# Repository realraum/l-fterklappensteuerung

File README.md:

# r3 Lüfterklappensteuerung

Damper-Control for ventilation exhaust system in realraum.

## Overview

The state of three dampers (open / closed) and one fan (running / not running)need to be controlled electronically.
Additionally two touchscreen interfaces shall be created to controll the damper states.

The three dampers control exhaust of :
- Lasercutter
- Atomic absorption spectrometer
- Laminaflow

The lasercutter is in a separate room with a separate touchscreen interface.

##### Constraints:

If a damper has been opened in one room, it can only be closed via the interface in that room. This is a safty measure so that dampers 
are not closed from a separate room by people unaware that the exhaust is still in use.

## Contents

### elektronik

see this folder on how to connect stuff.

### firmware

this folder contains the firmware for the uc

The µCs communicate via PJON protocol. At least one raspberry will communicate via usb-serial with one of the µC. Each µC can be a bridge between usb-serial and PJON-bus.

### mechanik

The dampers are controlled by cheap motors from neuhold.
Their position is known via a photoelectric fork and a lasercut disk with slots.

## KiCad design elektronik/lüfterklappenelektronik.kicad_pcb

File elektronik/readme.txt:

===== µC =====

ATMega32U4
5V
16MHz

===== 230VAC Lüfter =====

wird geschalten mit: Neuhold SSR Typ ZG3NC-240B
hängt im Phasenleiter.
Datasheet: http://www.ndu.cl/pdf/0509040FT.pdf
Schaltleistung: 40A mit eingebautem Snubber. bei induktiven Lasten: 40% Strom der 40A sind ok --> passt für unseren Motor uns seiner Startlastspitzen.

SSR zieht laut Datenblatt maximal 40mA
laut Tests: <13mA bei 5V und <6mA bei 3V (und <11mA bei 5V mit 100 Ohm Widerstand in Serie weil weniger Spannung am SSR anliegt was auf den Stromverbrauch rückwirkt)
-> müsste mit teensy2 pin als Senke fast ohne Transistorschalter direkt zu schalten möglich sein.
  da atmega32u4 laut datenblatt 20mA permanent per IO senken kann solange die Summe einer im Datenblatt definierten Gruppe von Ports nicht 100mA überschreitet.

Zusätzlich: Varistor für 230V parallel zum SSR:
--> S7K275 welche im r3 sind
oder alternativ S14K680 von Neuhold
oder notfalls: 2x S10K150 in Serie

generelle Infos:
http://www.crydom.com/en/tech/whitepapers/ac_mc_whitepaper.pdf
http://forum.arduino.cc/index.php?topic=114209.0

off leakage: 10mA = 10mA (SSR) + 0mA (Varistor)

===== 12V Getriebemotoren für Lüfterklappen =====

Wird geschalten mit PowerMosFET und Freilaufdiode.

MosFET: IPP029N06N, reicht für 5V
     (alternativ: IRLR8743pbf)

Freilaufdiode parallel zum Motor, gegen Stromrichtung, sollte für >8A dimensioniert sein
SBL10L25 od. Ähnliches

===== Gabellichtschranken =====

2k2 Ohm(?) an K Ausgang um Widerstand der Photodiode zu balancieren.

120 Ohm Vorwiderstand für die LED

===== Drucksensor =====
BMP280

==== TODO ====

test SSR directly am Teensy:

SSR LED pulls <=19mA per test and 40mA per datasheet
We _could_probably connect it directly to the Teensy via 12 Ohm R
or maybe 47Ohm R which means 2V drop on 40mA and 0.5V drop on 10mA so we may naturally limit the current.
Relay LED minimum Voltage is 3V

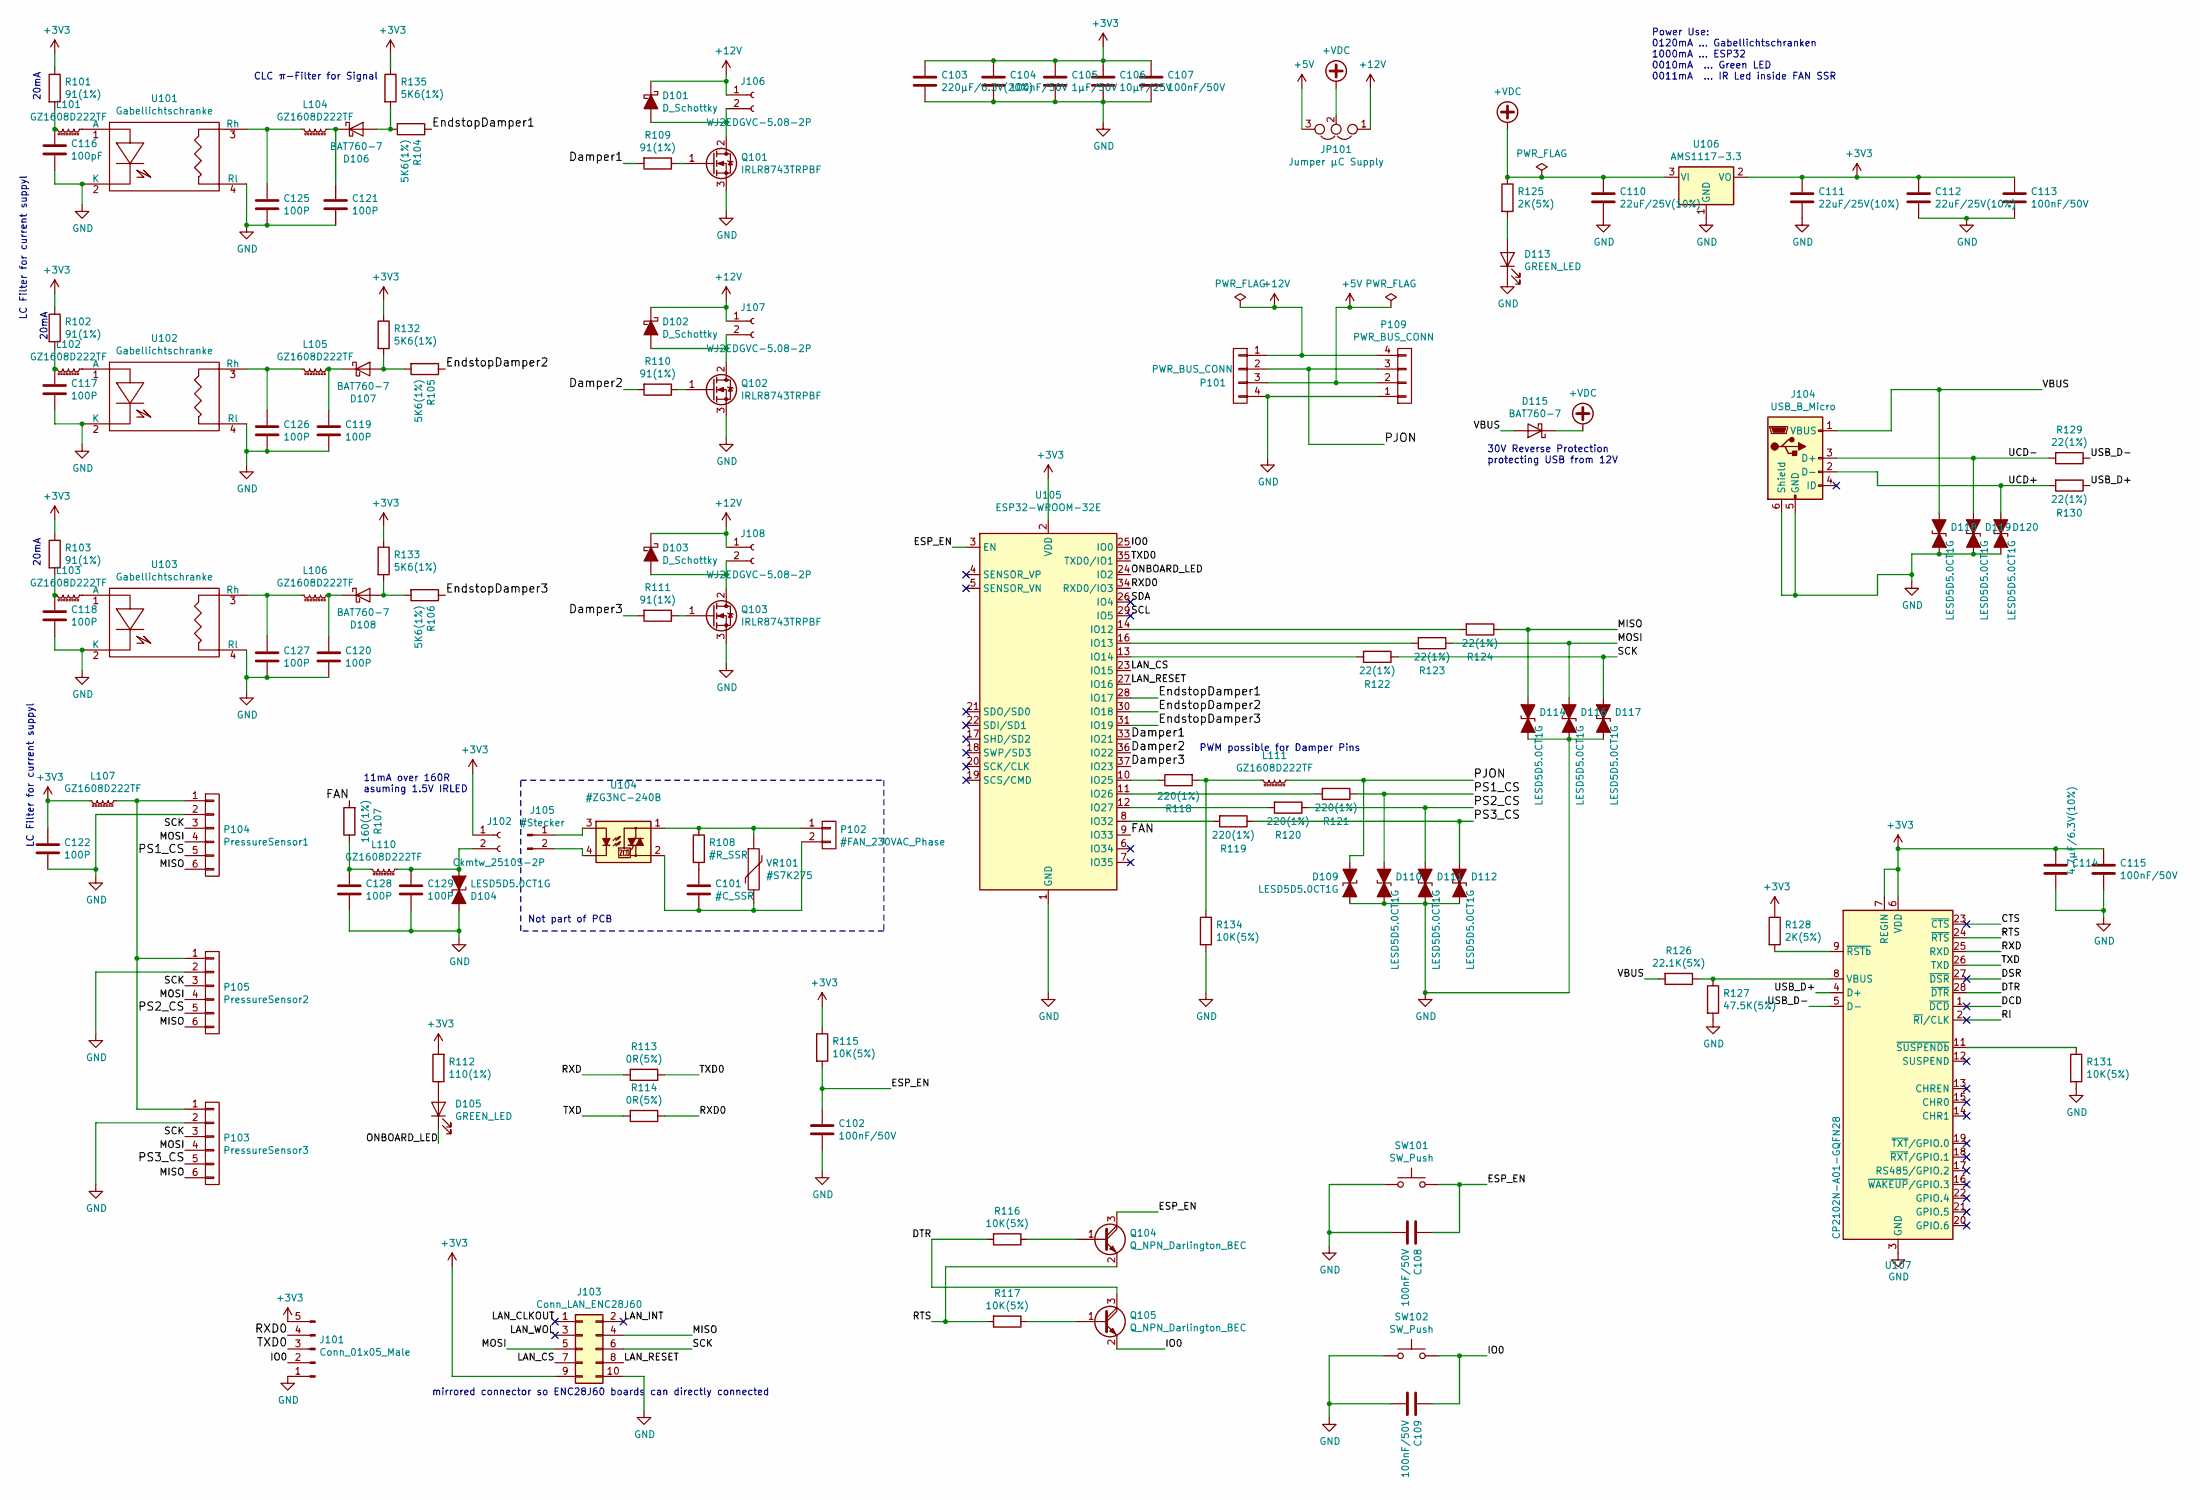
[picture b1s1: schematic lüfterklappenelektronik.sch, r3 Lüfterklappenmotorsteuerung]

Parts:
C101: #C_SSR
C102, C104, C107, C108, C109, C113, C115: 100nF/50V; C_0603_1608Metric; LCSCPartN C42998
C103: 220µF/6.3V(20%); C_1206_3216Metric; LCSCPartN C412252
C105: 1µF/50V; C_0603_1608Metric; LCSCPartN C105174
C106: 10µF/25V; C_0805_2012Metric; LCSCPartN C40894
C110, C111, C112: 22uF/25V(10%); C_1210_3225Metric; LCSCPartN C337455
C114: 4.7µF/6.3V(10%); C_0603
C116: 100pF; C_0603_1608Metric
C117, C118, C119, C120, C121, C122, C125, C126, C127, C128, C129: 100P; C_0603_1608Metric
D101, D102, D103: D_Schottky; D_SMB; LCSCPartN C353175
D104, D109, D110, D111, D112, D114, D116, D117, D118, D119, D120: LESD5D5.0CT1G; D_SOD-523; LCSCPartN C383211
D105, D113: GREEN_LED; LED_0603_1608Metric; LCSCPartN C264449
D106, D107, D108, D115: BAT760-7; D_SOD-323; LCSCPartN C124187
J101: Conn_01x05_Male; PinHeader_1x05_P2.54mm_Vertical
J102: Ckmtw_2510S-2P; C30436_pinhead_1x2_vertical_P2.54; LCSCPartN C30436
J103: Conn_LAN_ENC28J60; PinSocket_2x05_P2.54mm_Vertical_SMD
J104: USB_B_Micro; USB_Micro-B_C77238; LCSCPartN C77238
J105: #Stecker
J106, J107, J108: WJ2EDGVC-5.08-2P; LCSCPartN C8445
JP101: Jumper µC Supply; PinHeader_1x03_P2.54mm_Vertical
L101, L102, L103, L104, L105, L106, L107, L110, L111: GZ1608D222TF; L_0603_1608Metric_Pad1.05x0.95mm_HandSolder; LCSCPartN C96697
P101, P109: PWR_BUS_CONN; WJ2EDGRC-5.08-4P; LCSCPartN C8446
P102: #FAN_230VAC_Phase
P103: PressureSensor3; PinHeader_1x06_P2.54mm_Vertical
P104: PressureSensor1; PinHeader_1x06_P2.54mm_Vertical
P105: PressureSensor2; PinHeader_1x06_P2.54mm_Vertical
Q101, Q102, Q103: IRLR8743TRPBF; TO-252-2; LCSCPartN C51360
Q104, Q105: Q_NPN_Darlington_BEC; SOT-23; LCSCPartN C164885
R101, R102, R103, R109, R110, R111: 91(1%); R_0603_1608Metric
R104, R105, R106, R132, R133, R135: 5K6(1%); R_0603_1608Metric
R107: 160(1%); R_0603_1608Metric
R108: #R_SSR
R112: 110(1%); R_0603_1608Metric
R113, R114: 0R(5%); R_0603_1608Metric
R115, R116, R117, R131, R134: 10K(5%); R_0603_1608Metric
R118, R119, R120, R121: 220(1%); R_0603_1608Metric
R122, R123, R124, R129, R130: 22(1%); R_0603_1608Metric
R125, R128: 2K(5%); R_0603_1608Metric
R126: 22.1K(5%); R_0603_1608Metric
R127: 47.5K(5%); R_0603_1608Metric
SW101, SW102: SW_Push; SW_SPST_B3SL-1022P; LCSCPartN C86708
U101, U102, U103: Gabellichtschranke; Ckmtw_2510S-4P; LCSCPartN C140769
U104: #ZG3NC-240B
U105: ESP32-WROOM-32E; ESP32-WROOM-32; LCSCPartN C701343
U106: AMS1117-3.3; SOT-89-3; LCSCPartN C347256
U107: CP2102N-A01-GQFN28; QFN-28-1EP_5x5mm_P0.5mm_EP3.35x3.35mm; LCSCPartN C428937
VR101: #S7K275

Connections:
+3V3: C103.1, C104.1, C105.1, C106.1, C107.1, C111.1, C112.1, C113.1, C114.1, C115.1, C122.1, J101.5, J102.1, J103.9, L107.2, R101.1, R102.1, R103.1, R112.2, R115.1, R128.1, R132.1, R133.1, R135.1, U105.2 (VDD), U106.2 (VO), U107.6 (VDD), U107.7 (REGIN)
+5V: JP101.3, P101.3, P109.2
+12V: D101.1 (K), D102.1 (K), D103.1 (K), J106.1, J107.1, J108.1, JP101.1, P101.1, P109.4
+VDC: C110.1, D115.1 (K), JP101.2, R125.1, U106.3 (VI)
/CTS: U107.23 (~CTS)
/DCD: U107.1 (~DCD)
/DSR: U107.27 (~DSR)
/DTR: Q105.3 (C), R116.2, U107.28 (~DTR)
/Damper1: R109.2, U105.33 (IO21)
/Damper2: R110.2, U105.36 (IO22)
/Damper3: R111.2, U105.37 (IO23)
/ESP_EN: C102.1, C108.1, Q104.3 (C), R115.2, SW101.2, U105.3 (EN)
/EndstopDamper1: R104.1, U105.28 (IO17)
/EndstopDamper2: R105.1, U105.30 (IO18)
/EndstopDamper3: R106.1, U105.31 (IO19)
/FAN: R107.2, U105.9 (IO33)
/IO0: C109.1, J101.2, Q105.2 (E), SW102.2, U105.25 (IO0)
/LAN_CLKOUT: J103.1
/LAN_CS: J103.7, U105.23 (IO15)
/LAN_INT: J103.2
/LAN_RESET: J103.8, U105.27 (IO16)
/LAN_WOL: J103.3
/MISO: D114.1 (A1), J103.4, P103.6, P104.6, P105.6, R124.1
/MOSI: D116.1 (A1), J103.5, P103.4, P104.4, P105.4, R123.1
/ONBOARD_LED: D105.1 (K), U105.24 (IO2)
/PJON: D109.1 (A1), L111.1, P101.2, P109.3
/PS1_CS: D110.1 (A1), P104.5, R121.1
/PS2_CS: D111.1 (A1), P105.5, R120.1
/PS3_CS: D112.1 (A1), P103.5, R119.1
/RI: U107.2 (~RI~/CLK)
/RTS: Q104.2 (E), R117.2, U107.24 (~RTS)
/RXD: R113.2, U107.25 (RXD)
/RXD0: J101.4, R114.1, U105.34 (RXD0/IO3)
/SCK: D117.1 (A1), J103.6, P103.3, P104.3, P105.3, R122.1
/SCL: U105.29 (IO5)
/SDA: U105.26 (IO4)
/TXD: R114.2, U107.26 (TXD)
/TXD0: J101.3, R113.1, U105.35 (TXD0/IO1)
/UCD+: D120.1 (A1), J104.2 (D-), R130.2
/UCD-: D119.1 (A1), J104.3 (D+), R129.2
/USB_D+: R130.1, U107.4 (D+)
/USB_D-: R129.1, U107.5 (D-)
/VBUS: D115.2 (A), D118.1 (A1), J104.1 (VBUS), R126.2
GND: C102.2, C103.2, C104.2, C105.2, C106.2, C107.2, C108.2, C109.2, C110.2, C111.2, C112.2, C113.2, C114.2, C115.2, C116.2, C117.2, C118.2, C119.2, C120.2, C121.2, C122.2, C125.2, C126.2, C127.2, C128.2, C129.2, D104.1 (A1), D109.2 (A2), D110.2 (A2), D111.2 (A2), D112.2 (A2), D113.1 (K), D114.2 (A2), D116.2 (A2), D117.2 (A2), D118.2 (A2), D119.2 (A2), D120.2 (A2), J101.1, J103.10, J104.5 (GND), J104.6 (Shield), P101.4, P103.2, P104.2, P105.2, P109.1, Q101.3 (S), Q102.3 (S), Q103.3 (S), R127.2, R131.2, R134.2, SW101.1, SW102.1, U101.2 (K), U101.4 (Rl), U102.2 (K), U102.4 (Rl), U103.2 (K), U103.4 (Rl), U105.1 (GND), U105.15 (GND), U105.38 (GND), U105.39 (GND), U106.1 (GND), U107.3 (GND), U107.29 (GND)
unnamed: C101.1, R108.2
unnamed: C101.2, P102.2, U104.2, VR101.2
unnamed: C116.1, L101.2, R101.2
unnamed: C117.1, L102.2, R102.2
unnamed: C118.1, L103.2, R103.2
unnamed: C119.1, D107.1 (K), L105.1
unnamed: C120.1, D108.1 (K), L106.1
unnamed: C121.1, D106.1 (K), L104.1
unnamed: C125.1, L104.2, U101.3 (Rh)
unnamed: C126.1, L105.2, U102.3 (Rh)
unnamed: C127.1, L106.2, U103.3 (Rh)
unnamed: C128.1, L110.2, R107.1
unnamed: C129.1, D104.2 (A2), J102.2, L110.1
unnamed: D101.2 (A), J106.2, Q101.2 (D)
unnamed: D102.2 (A), J107.2, Q102.2 (D)
unnamed: D103.2 (A), J108.2, Q103.2 (D)
unnamed: D105.2 (A), R112.1
unnamed: D106.2 (A), R104.2, R135.2
unnamed: D107.2 (A), R105.2, R132.2
unnamed: D108.2 (A), R106.2, R133.2
unnamed: D113.2 (A), R125.2
unnamed: J105.1, U104.3
unnamed: J105.2, U104.4
unnamed: L101.1, U101.1 (A)
unnamed: L102.1, U102.1 (A)
unnamed: L103.1, U103.1 (A)
unnamed: L107.1, P103.1, P104.1, P105.1
unnamed: L111.2, R118.2, R134.1
unnamed: P102.1, R108.1, U104.1, VR101.1
unnamed: Q101.1 (G), R109.1
unnamed: Q102.1 (G), R110.1
unnamed: Q103.1 (G), R111.1
unnamed: Q104.1 (B), R116.1
unnamed: Q105.1 (B), R117.1
unnamed: R118.1, U105.10 (IO25)
unnamed: R119.2, U105.8 (IO32)
unnamed: R120.2, U105.12 (IO27)
unnamed: R121.2, U105.11 (IO26)
unnamed: R122.2, U105.13 (IO14)
unnamed: R123.2, U105.16 (IO13)
unnamed: R124.2, U105.14 (IO12)
unnamed: R126.1, R127.1, U107.8 (VBUS)
unnamed: R128.2, U107.9 (~RSTb)
unnamed: R131.1, U107.11 (~SUSPENDb)

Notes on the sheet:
30V Reverse Protection protecting USB from 12V
11mA over 160R asuming 1.5V IRLED
20mA
Power Use: 0120mA ... Gabellichtschranken 1000mA ... ESP32 0010mA ... Green LED 0011mA ... IR Led inside FAN SSR
mirrored connector so ENC28J60 boards can directly connected
PWM possible for Damper Pins
Not part of PCB
LC Filter for current suppyl
CLC π-Filter for Signal

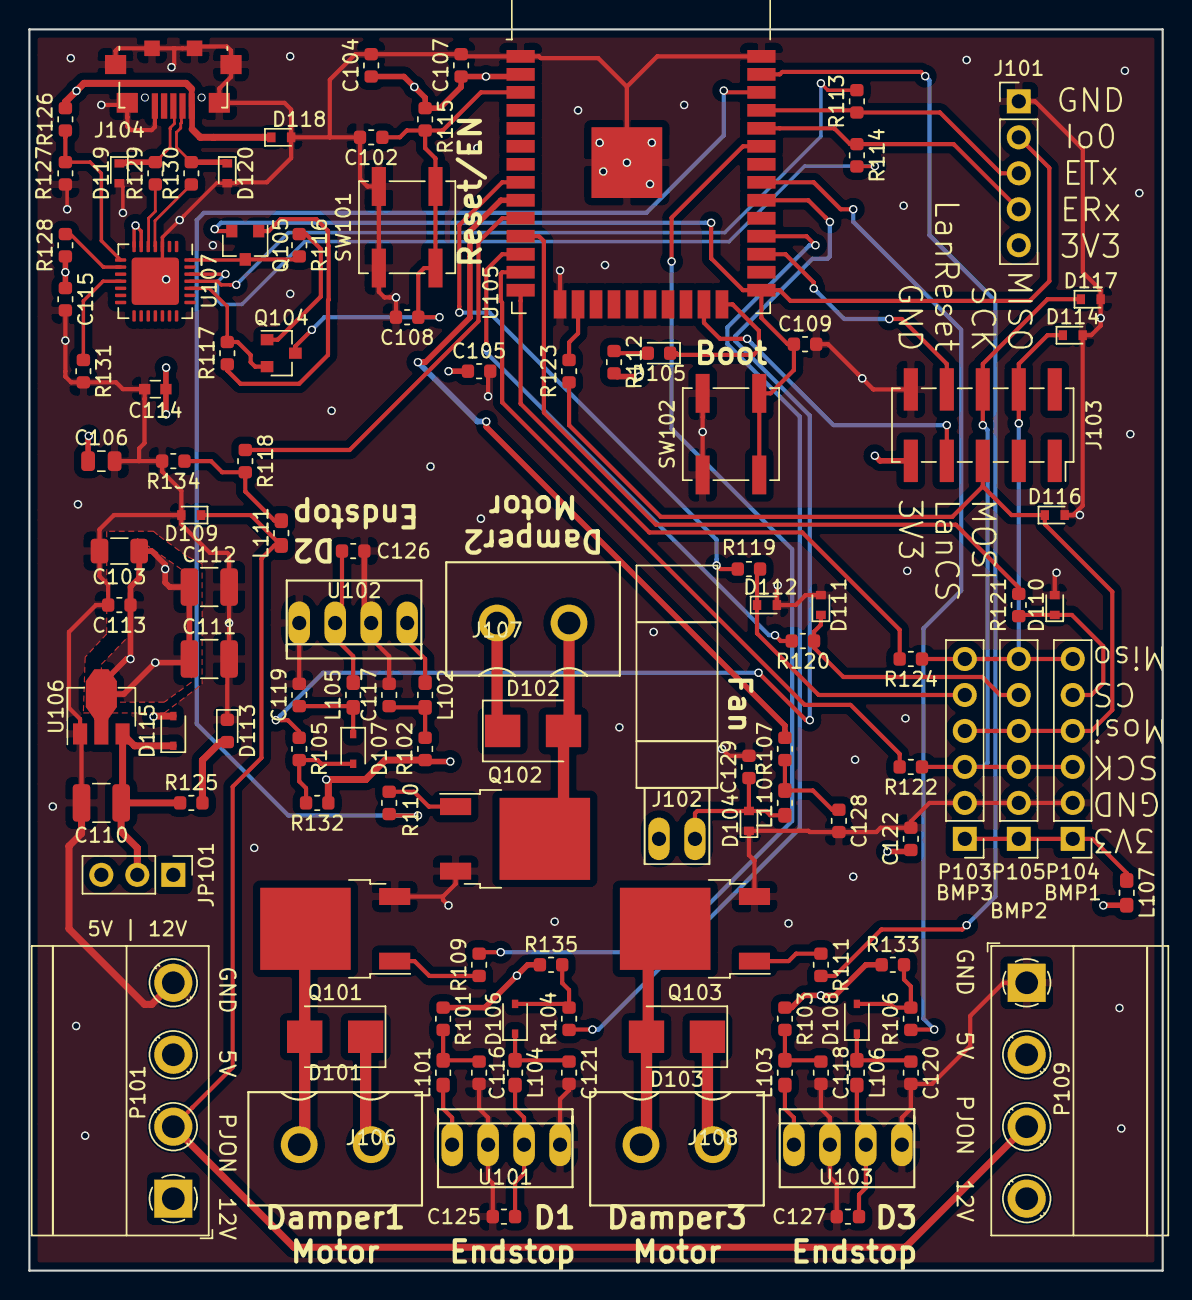
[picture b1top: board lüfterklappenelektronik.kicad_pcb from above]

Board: 4 copper layers, 80.0 x 87.6 mm, 115 parts (0 on the bottom side), 74 nets.

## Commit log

2016-05-22 initial commit, some planning, some work done
2016-05-27 avr utils framework
2016-05-28 thoughts compile, ready to do some programming
2016-05-28 good inital code state
2016-05-28 prepare pressure sensor
2016-05-29 pressure
2016-05-29 lot's of debugging makes things work
2016-05-30 doku, improvements, tested valued
2016-05-30 -- stupid bug
2016-05-30 separate msg length calc
2016-05-30 readme
2016-05-30 dump out pjon bus packets and warn if endstop not reached in time
2016-05-30 make enum 'private' and move to where it's used
2016-05-30 guess initial state works, but is not reliable
2016-05-30 instead, on init seek 0 position or send error on start
2016-05-30 notes and todo
2016-06-03 fixed path to PJON
2016-06-05 pin changes for arduinoProMicro
2016-06-05 some never to be used routing
2016-06-05 fix symbol
2016-06-05 update pjon pin
2016-06-10 fix_pjon_pin
2016-06-10 test
2016-06-12 ProMicro and PressureSensor
2016-06-12 only send every few seconds or so
2016-06-12 besser als gar keine doku
2016-06-19 placeholder
2016-06-21 fix pins
2016-06-21 fix fan logic
2016-06-21 todos
2016-06-21 todo
2016-06-22 dualacm
2016-06-27 first draft
2016-08-05 untested
2016-09-18 compilefix
2016-09-22 autoorder pjon ids
2016-09-23 don't sort in all the zeros of unused elements
2016-10-02 become master
2016-10-17 exchange streams 0 and 1
2016-10-17 Revert "exchange streams 0 and 1"
    This reverts commit 277c6806d903831333514e7d8f6e80aa0e8d3655.
2016-10-17 Revert "dualacm"
    This reverts commit 24d715dcdd4bca1b28ec506e97399848078f2a11.
2016-10-17 debugging operations
2016-10-17 use correct name of pjon_device_id_
2016-10-18 handle incoming pjon msg after ack' it
2016-10-19 let µC send dampercmds directly
2016-10-19 reintroduce PJON msg injection from first tty (and keep door open for future reintroduction of second tty)
2016-10-19 should not matter, maybe cleaner
2016-10-19 correct misleading debug output (PJON msgs do not contain from information)
2016-10-19 reorder and comment
2016-10-19 minor bugfix
2016-10-27 more debugging options
2016-10-27 oszi screenshot
2016-10-27 --bug: chaincast msg passes µc on top of ladder only once
2016-10-27 lot's of electrical and firmware todo's done
2016-11-05 fan for lamina flow
2016-11-05 FAN_ON is FAN_AUTO
2016-11-05 add second fan control
2016-11-08 first attempt at retry-after-fail-code, but not very statisfying
2017-06-16 html interface
2017-06-16 webinterface webserver daemon
2017-09-05 send commands
2017-09-05 white fan
2017-09-05 valid inital empty state
2017-09-05 fixes
2017-09-06 layout for 320x240 epiphany and rename
2017-09-06 script to create pre-configured raspberry image
2017-09-12 fix disable blanking/dpms
2017-09-12 still using old protocol
2017-09-12 ro /
2017-09-12 lightdm needs write to home? to start user
2017-09-12 extra home
2017-09-12 can't hurt
2017-09-12 experiment with hack
2017-09-21 disable dhcp for interface
2017-09-27 udev rule
2017-09-28 improve
2017-09-28 fine tune position default
2017-09-28 waiting animation and make_deploy
2017-09-28 convenient evil
2017-09-28 no more lightdm
2017-09-28 webkit sucks chromium works
2017-10-01 better loading image
2017-10-04 a bit more sanity checking
2017-10-04 working error messages
2017-10-04 mqtt support
2017-10-04 all the ventilation code
2018-01-18 longer timeout
2018-01-18 send request to be sanity checked instead of just shutting off
2018-01-18 don't loop timers forever
2018-01-18 only switch off if nobody here after 2 minutes
2018-01-18 configurable timeout
2018-01-21 handle local and authenticated OLGA Lock Change
2018-01-21 start with inital state, even if unknown, so users are not confused
2018-01-21 webinterface js needs testing
2018-01-26 rewrite lock and token code so it all works
2018-01-26 finetune sanitycheck
2019-04-06 debugging
2019-04-06 ignore endstop trigger when motor is not turning
2019-04-06 markdown
2019-04-06 --typo
2020-10-28 esp32 start
2020-10-28 rescue
2020-10-28 symlib
2020-10-29 esp32 schaltung
2020-10-30 nice looking schematic
2020-10-30 selected all footprints and components
2020-10-30 update footprint
2020-10-30 fixed connectors
2020-10-30 fixed footprints of R and Diode
2020-10-30 ready to layout
2020-10-30 fix LAN port
2020-10-31 place some groups
2020-11-12 rough placing
2020-11-12 added more noise and transient protection
2020-11-17 placing mostly done
2020-11-17 placing improved
2020-11-17 basic routing, drc passed
2020-11-17 power routing, drc passed
2020-11-17 beautify routing, drc passed
2020-11-17 done
2020-11-17 fixes. One fuckup remaining: damper2 needs different connector now
2020-11-17 fixed part, footprint still needs fixing
2020-11-18 change to vertical footprint and make some space for corrently sized courtyards
2020-11-18 update bom info and remove rescues
2020-11-20 config
2020-12-16 fix holesize
2020-12-16 export v2
2020-12-17 schema: change footprint to vertical
2020-12-17 pcbnew: change footprint to vertical and fix fillzones and traces
2020-12-17 pcbnew: improve silk layer
2021-01-23 throw out the old, pave way for rewriting
2021-02-01 on the way to first PCB test
2021-08-12 gomodules
2021-08-21 raspios changes bugfixes
2021-08-21 now a system service since linger no longer works without boot
2021-12-17 closer to working X
2021-12-18 custom calibration
